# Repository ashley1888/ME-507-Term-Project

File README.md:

# ME-507-Term-Project
Claw Machine by

Michael Yiu and Ashley Humpal

Fall 2021

The code in this repository aims to control a claw machine and have it go to a destination and pick up objects.

For formal documentation please refer to: https://ashley1888.github.io/ME-507-Term-Project/

This repository contains:

controller_task.cpp

controller_task.h

X_Motor_task.cpp

X_Motor_task.h

Y_Motor_task.cpp

Y_Motor_task.h

Z_Motor_task.cpp

Z_Motor_task.h

Gripper_Motor_task.cpp

Gripper_Motor_task.h

motor_driver.cpp

motor_driver.h

shares.h

main.cpp

Encoder driver files were provided by our professor, Dr. Ridgely and their source code can be found at:
https://github.com/spluttflob/ME507-Support/blob/master/examples/encoder_counter.cpp
https://github.com/spluttflob/ME507-Support/blob/master/examples/encoder_counter.h

Each file contains doxygen style documentation.

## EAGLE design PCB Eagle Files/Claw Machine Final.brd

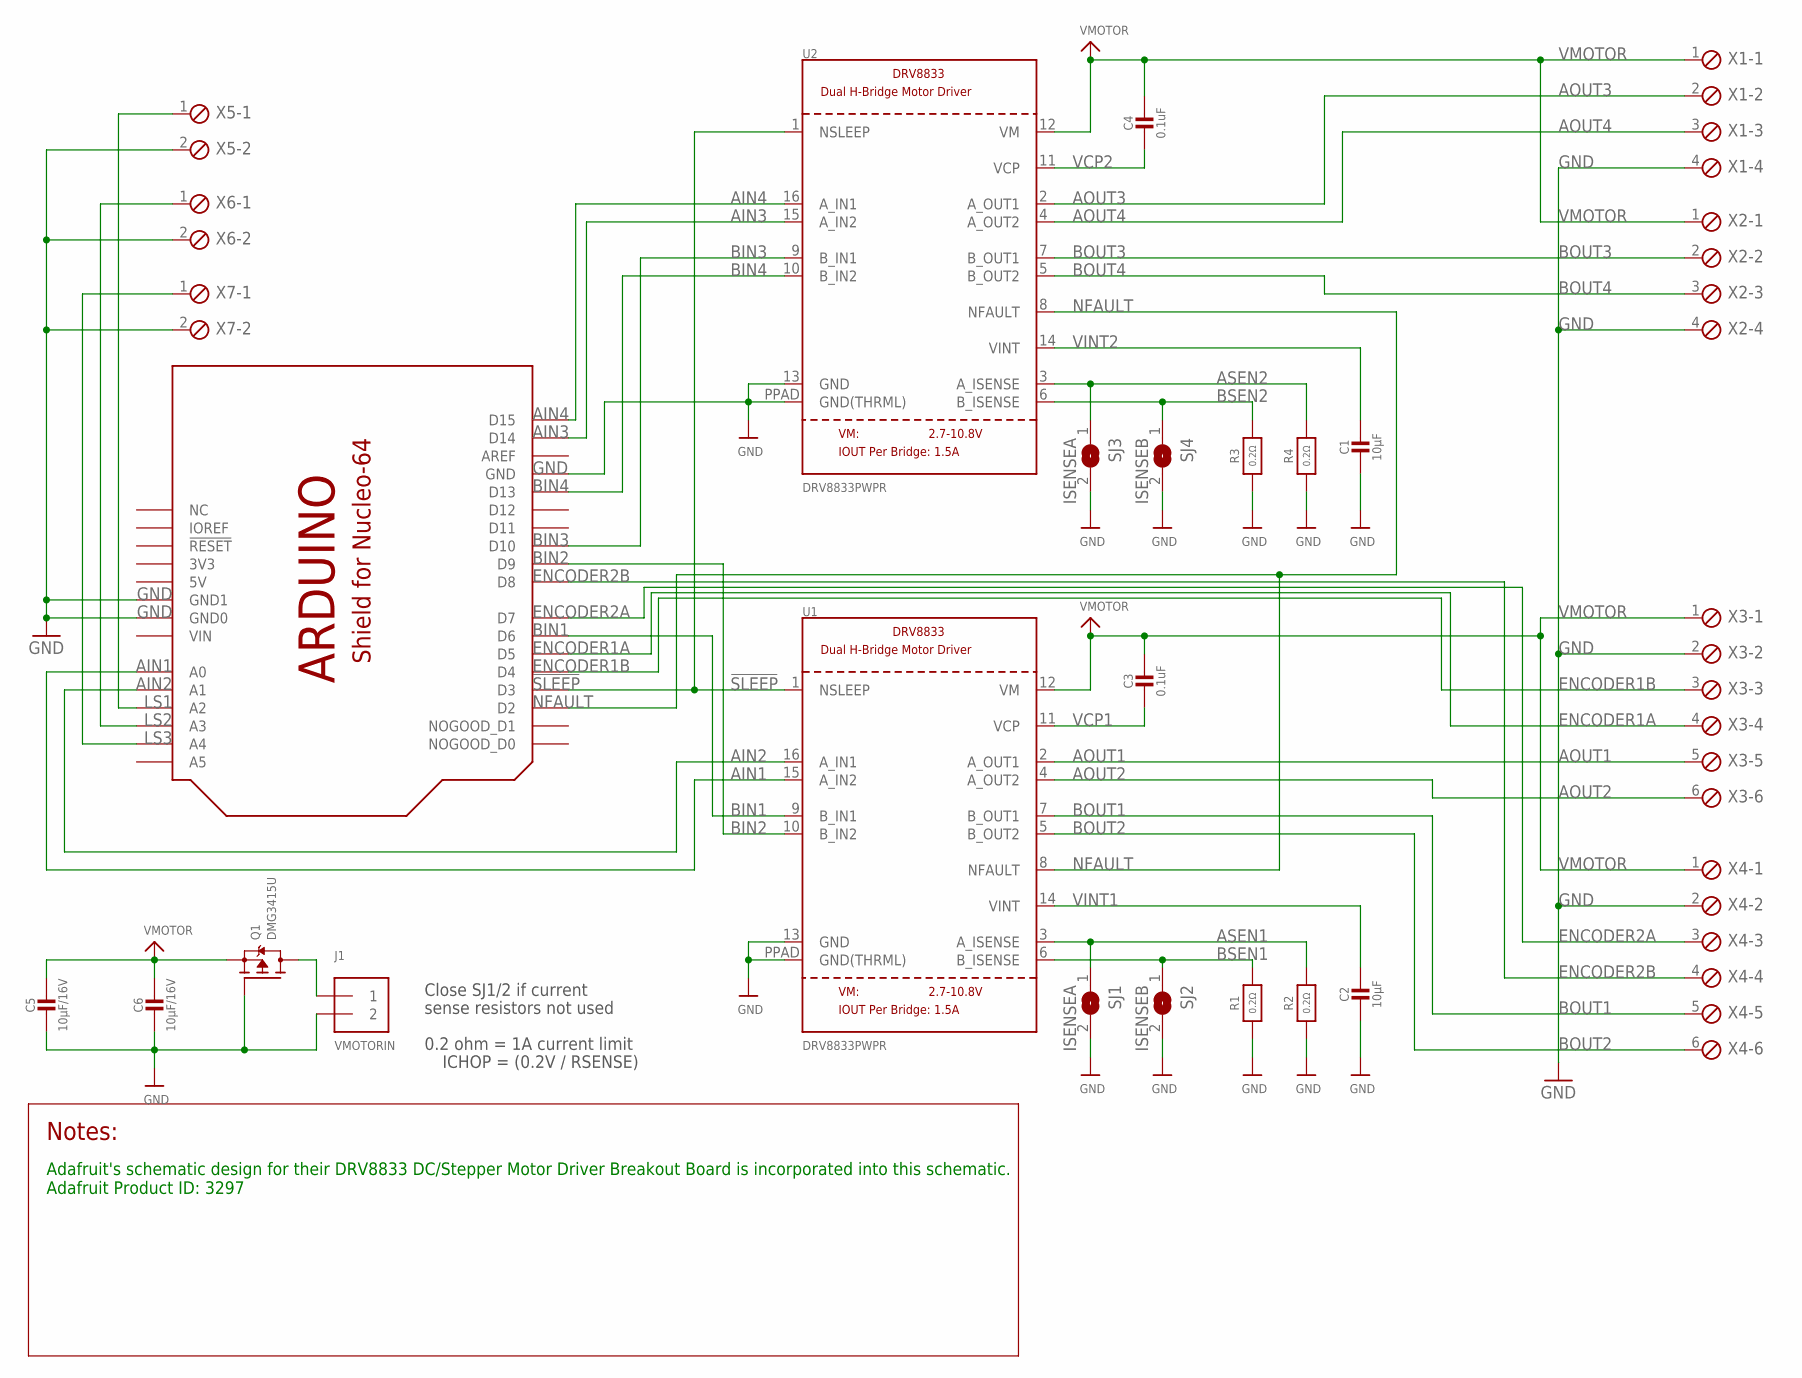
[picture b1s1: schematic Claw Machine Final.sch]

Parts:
C1, C2: 10µF; 0805-NO
C3, C4: 0.1uF; 0805-NO
C5, C6: 10µF/16V; 0805-NO
J1: VMOTORIN; TERMBLOCK_1X2-3.5MM
Q1: DMG3415U; SOT23-WIDE
R1, R2, R3, R4: 0.2Ω; _1206
SJ1, SJ3: ISENSEA; SOLDERJUMPER_ARROW_NOPASTE
SJ2, SJ4: ISENSEB; SOLDERJUMPER_ARROW_NOPASTE
U1, U2: DRV8833PWPR; HTSSOP16
U$1: SHIELD_FOR_NUCLE0_64_STANDARD; SHIELD_FOR_NUCLEO_64_STD
X1, X2: SCREWTERM_4P_254; 4POL254
X3, X4: SCREWTERM_6P_254; 6POL254
X5, X6, X7: SCREWTERM_2P_254; 2POL254

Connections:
3V3: U$1.3V (3V3)
5V: U$1.5V
!SLEEP: U1.1 (NSLEEP), U2.1 (NSLEEP), U$1.D3
AIN1: U1.15 (A_IN2), U$1.A0
AIN2: U1.16 (A_IN1), U$1.A1
AIN3: U2.15 (A_IN2), U$1.D14
AIN4: U2.16 (A_IN1), U$1.D15
AOUT1: U1.2 (A_OUT1), X3.5
AOUT2: U1.4 (A_OUT2), X3.6
AOUT3: U2.2 (A_OUT1), X1.2
AOUT4: U2.4 (A_OUT2), X1.3
ASEN1: R2.2, SJ1.1, U1.3 (A_ISENSE)
ASEN2: R4.2, SJ3.1, U2.3 (A_ISENSE)
BIN1: U1.9 (B_IN1), U$1.D6
BIN2: U1.10 (B_IN2), U$1.D9
BIN3: U2.9 (B_IN1), U$1.D10
BIN4: U2.10 (B_IN2), U$1.D13
BOUT1: U1.7 (B_OUT1), X4.5
BOUT2: U1.5 (B_OUT2), X4.6
BOUT3: U2.7 (B_OUT1), X2.2
BOUT4: U2.5 (B_OUT2), X2.3
BSEN1: R1.2, SJ2.1, U1.6 (B_ISENSE)
BSEN2: R3.2, SJ4.1, U2.6 (B_ISENSE)
ENCODER1A: U$1.D5, X3.4
ENCODER1B: U$1.D4, X3.3
ENCODER2A: U$1.D7, X4.3
ENCODER2B: U$1.D8, X4.4
GND: C1.2, C2.2, C5.2, C6.2, J1.2, Q1.1 (G), R1.1, R2.1, R3.1, R4.1, SJ1.2, SJ2.2, SJ3.2, SJ4.2, U1.13 (GND), U1.PPAD (GND(THRML)), U2.13 (GND), U2.PPAD (GND(THRML)), U$1.GND, U$1.GND1 (GND0), U$1.GND2 (GND1), X1.4, X2.4, X3.2, X4.2, X5.2, X6.2, X7.2
LS1: U$1.A2, X5.1
LS2: U$1.A3, X6.1
LS3: U$1.A4, X7.1
NFAULT: U1.8 (NFAULT), U2.8 (NFAULT), U$1.D2
PWRIN: J1.1, Q1.3 (D)
VCP1: C3.2, U1.11 (VCP)
VCP2: C4.2, U2.11 (VCP)
VIN: U$1.VIN
VINT1: C2.1, U1.14 (VINT)
VINT2: C1.1, U2.14 (VINT)
VMOTOR: C3.1, C4.1, C5.1, C6.1, Q1.2 (S), U1.12 (VM), U2.12 (VM), X1.1, X2.1, X3.1, X4.1

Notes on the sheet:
Close SJ1/2 if current
sense resistors not used
0.2 ohm = 1A current limit
ICHOP = (0.2V / RSENSE)
Adafruit's schematic design for their DRV8833 DC/Stepper Motor Driver Breakout Board is incorporated into this schematic. Adafruit Product ID: 3297

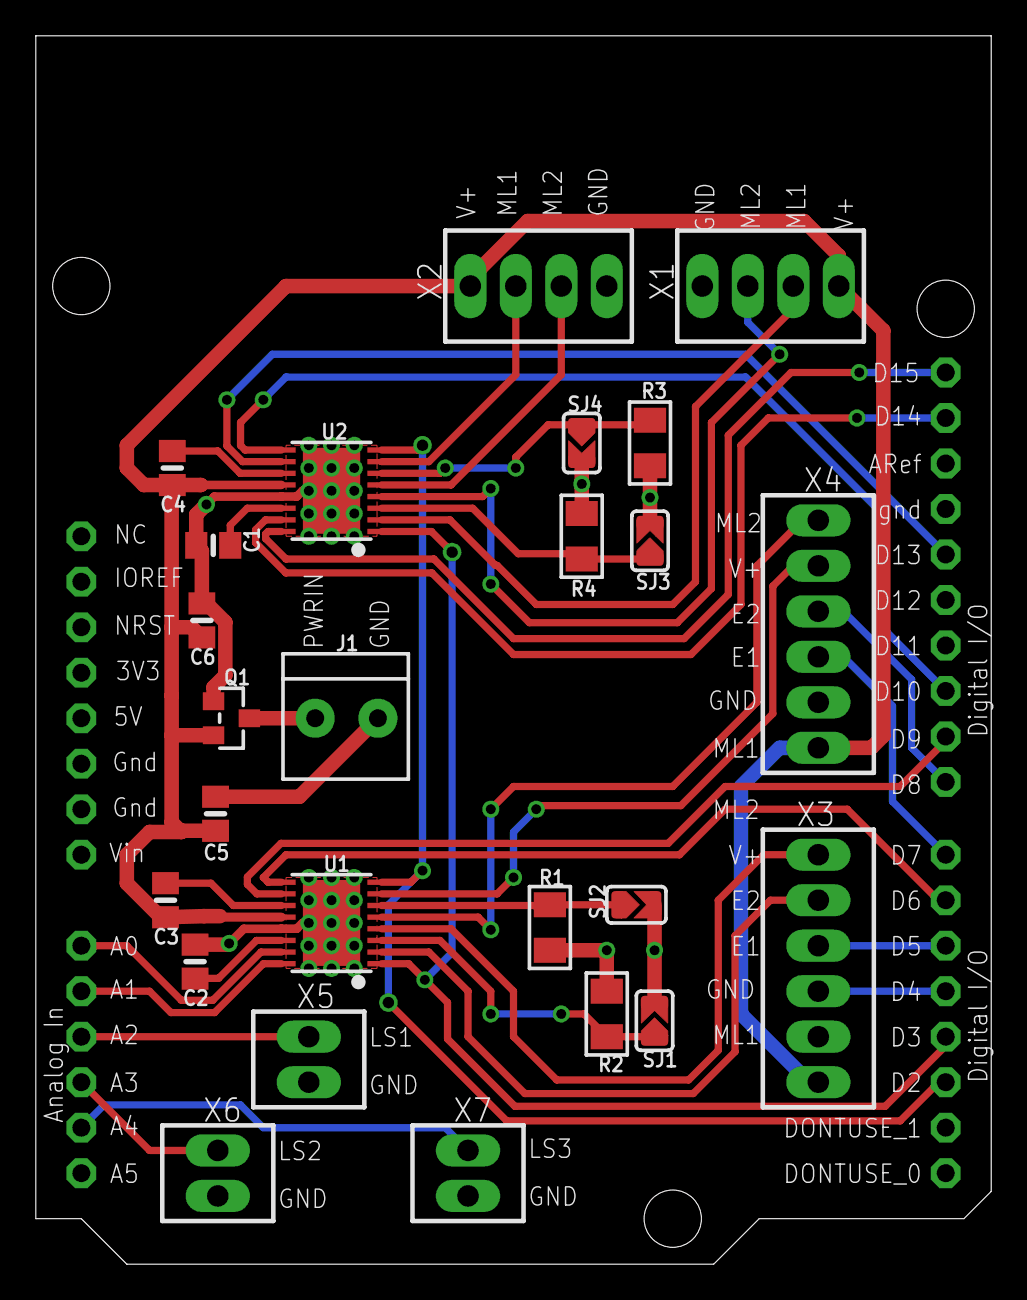
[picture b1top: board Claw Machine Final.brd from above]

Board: 2 copper layers, 53.3 x 68.6 mm, 26 parts (0 on the bottom side), 36 nets.

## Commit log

2021-11-18 Testing again
2021-11-23 Creating initial motor and encoder drivers
2021-11-23 Ridgley's Encoder Drivers added
2021-11-23 Encoder Task created
2021-11-24 creating shares and starting to make tasks
2021-11-24 modifying motor1 task so it checks shared values
2021-11-24 Created controller task
2021-11-25 trying to set up docs
2021-11-28 Trying to fix shares
2021-11-28 added shares job status and stopping motor when back at origin
2021-11-28 update lib deps
2021-11-28 didnt get a chance to review code, worked on the report and prepped some files for 3D printing
2021-11-28 Fixed shares lib deps issue
2021-11-29 creating task error fixed and new function error found
2021-11-29 error comment
2021-11-30 Moved files to new folder, and changed encoder code to work for PA0 and PA1
2021-11-30 motor 1 task
2021-11-30 edit controller task
2021-12-01 x&y motor tasks complete
2021-12-01 testing two motors
2021-12-01 cleaned up motor tasks
2021-12-01 adding shares to motor driver
2021-12-01 changed to remove an error message
2021-12-01 added to integrate controller task
2021-12-01 formating, added shares and added tasks: Z motor and Gripper motor
2021-12-01 formatting
2021-12-01 trying to incorporate shares
2021-12-01 Z motor task
2021-12-01 changed to correct pins (top right)
2021-12-01 was missing a comma
2021-12-01 commented code out to test (shares.put() or .get() is not working as expected)
2021-12-02 all 4 motor tasks created
2021-12-02 semi working controller
2021-12-02 controller test main
2021-12-02 testing shares
2021-12-02 faulted func added to motor driver
2021-12-02 incorporating shares
2021-12-02 nfault pin
2021-12-02 added PA10 for fault detection
2021-12-02 Integrating user input to controller task
2021-12-02 changed to shares instead of queues
2021-12-02 Added y user input to controller task
2021-12-02 motor inertia
2021-12-02 y shares
2021-12-02 added condition for if duty==0
2021-12-02 x motor task complete with shares
2021-12-02 x&y motors integrated w shares
2021-12-02 Added Chess Positions to Controller Task
2021-12-02 full systems integration
2021-12-02 revert
2021-12-02 cleaned merges
2021-12-02 disabled motor as a solution for now
2021-12-02 reverted last commit
2021-12-02 push
2021-12-06 Deleted uneccessary files
2021-12-07 cleaning up controller documentation
2021-12-07 Documentation for controller task cpp done
2021-12-07 documentation for controller.h done
2021-12-07 credited encoder files source in documentation
2021-12-07 editing z-motor task documentation
2021-12-07 finished gripper documentation
2021-12-07 Motor driver documentation done
2021-12-07 Documented shares
2021-12-07 documentation for the x motors
2021-12-07 y motor task documentation done
2021-12-07 z motor documented
2021-12-07 cleaning documentation
2021-12-07 Github webpage updates
2021-12-07 webpage documentation retry
2021-12-07 main documentation
2021-12-07 fixed main github documentation
2021-12-07 edit to controller task
2021-12-07 Added PCB files
2021-12-08 moved folders
2021-12-08 STL files
2021-12-08 3D Printer instructions
2021-12-08 added some documentation
2021-12-08 mainpage doc
2021-12-08 edited format
2021-12-08 Push fixed documentation
2021-12-08 added page and motor tasks
2021-12-08 added controller task page
2021-12-08 Update README.md
    test
2021-12-08 Update README.md
    updated readme to include all files
2021-12-08 Update README.md
    added spacing
2021-12-08 Update README.md
    testing
2021-12-08 Update README.md
    formating
2021-12-08 Update README.md
    formatting
2021-12-08 push conflicting changes
2021-12-08 doc image
2021-12-08 webpage documentation
2021-12-08 added task diagram image
2021-12-08 updating website
2021-12-08 change page name
2021-12-08 fixing the website
2021-12-08 added new page
2021-12-08 new page
2021-12-08 3D printed parts page
2021-12-08 images
2021-12-08 added images for 3D printed parts section and isometric view to introduction
2021-12-08 changed verbage
2021-12-08 whole file assembly
2021-12-08 changes it so the default folder it puts everything in is called "docs" instead of "html"
2023-04-22 Update README.md
    Added link to website.
